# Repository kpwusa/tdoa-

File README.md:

# tdoa-
time distance of arrival direction finder

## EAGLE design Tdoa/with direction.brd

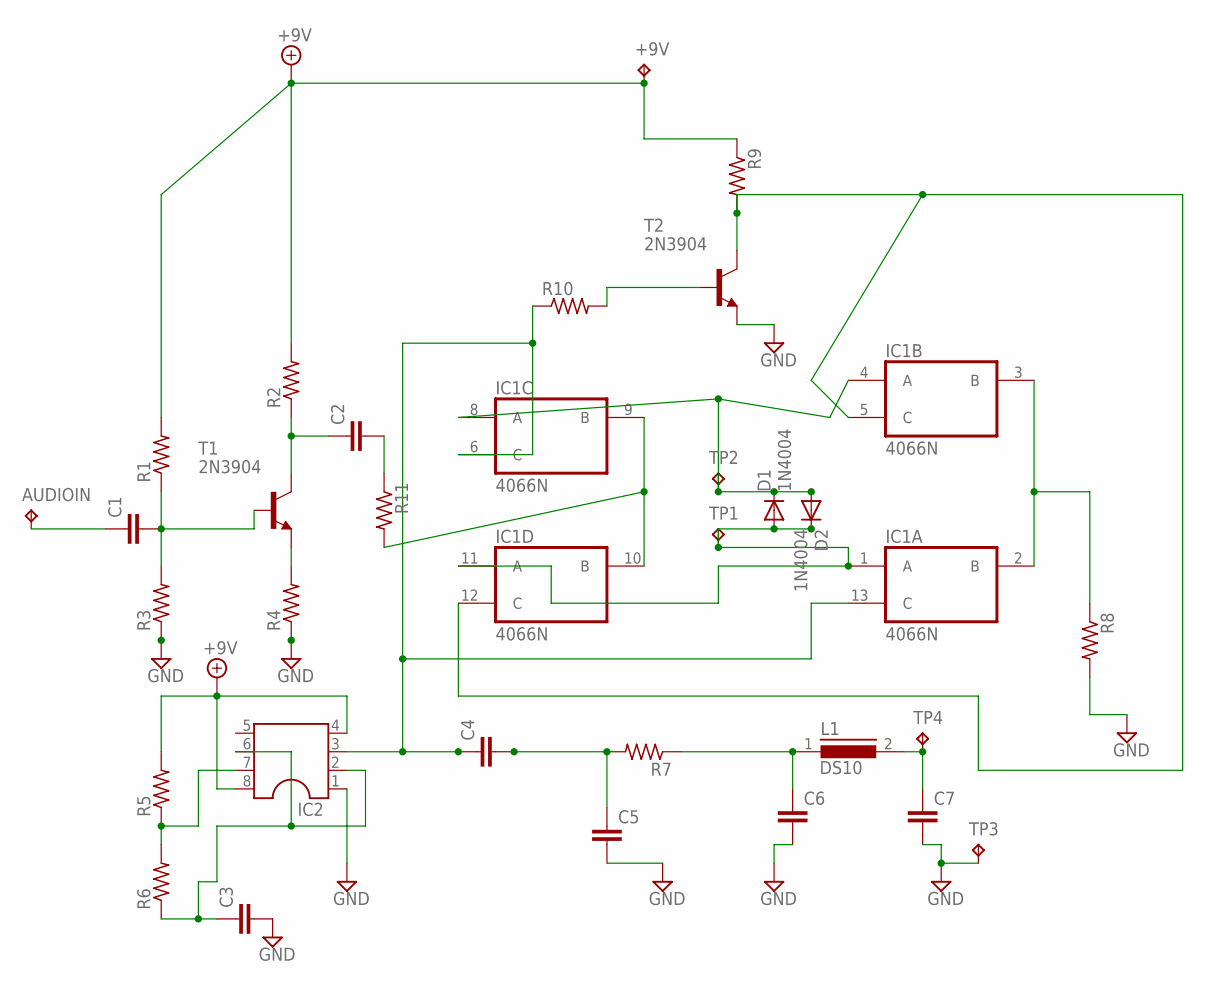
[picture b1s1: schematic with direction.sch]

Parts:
+9V: TPPAD1-17; P1-17
AUDIOIN: TPPAD1-17; P1-17
C1, C2, C7: C10/5; C10B5
C3, C4: C5/2.5; C5B2.5
C5, C6: C5/3; C5B3
D1, D2: 1N4004; DO41-10
IC1: 4066N; DIL14
IC2: DIL8S; SOCKET-08
L1: DS10
R1, R2, R3, R4, R5, R6, R7, R8, R10: R-US_0207/10; 0207/10
R9, R11: R-US_0207/15; 0207/15
T1, T2: 2N3904; TO92
TP1, TP2: TPPAD1-17; P1-17
TP3, TP4: TPPAD1-17Y; P1-17Y

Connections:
+9V: +9V.TP, IC1.14 (VDD), IC2.4, IC2.8, R1.2, R2.2, R5.2, R9.1
unnamed: AUDIOIN.TP, C1.1
unnamed: C1.2, R1.1, R3.2, T1.2 (B)
unnamed: C2.1, R2.1, T1.1 (C)
unnamed: IC1.5 (C), IC1.12 (C), R9.2, T2.1 (C)
unnamed: R10.2, T2.2 (B)
unnamed: C4.1, IC1.6 (C), IC1.13 (C), IC2.3, R10.1
unnamed: D1.C, D2.A, IC1.4 (A), IC1.8 (A), TP2.TP
unnamed: D1.A, D2.C, IC1.1 (A), IC1.11 (A), TP1.TP
unnamed: IC1.9 (B), IC1.10 (B), R11.2
unnamed: C2.2, R11.1
unnamed: IC1.2 (B), IC1.3 (B), R8.1
unnamed: C6.1, L1.1, R7.1
unnamed: C7.1, L1.2, TP4.TP
unnamed: R4.2, T1.3 (E)
unnamed: C4.2, C5.1, R7.2
unnamed: IC2.7, R5.1, R6.2
unnamed: C3.1, IC2.2, IC2.6, R6.1
VSS: C3.2, C5.2, C6.2, C7.2, IC1.7 (VSS), IC2.1, R3.1, R4.1, R8.2, T2.3 (E), TP3.TP

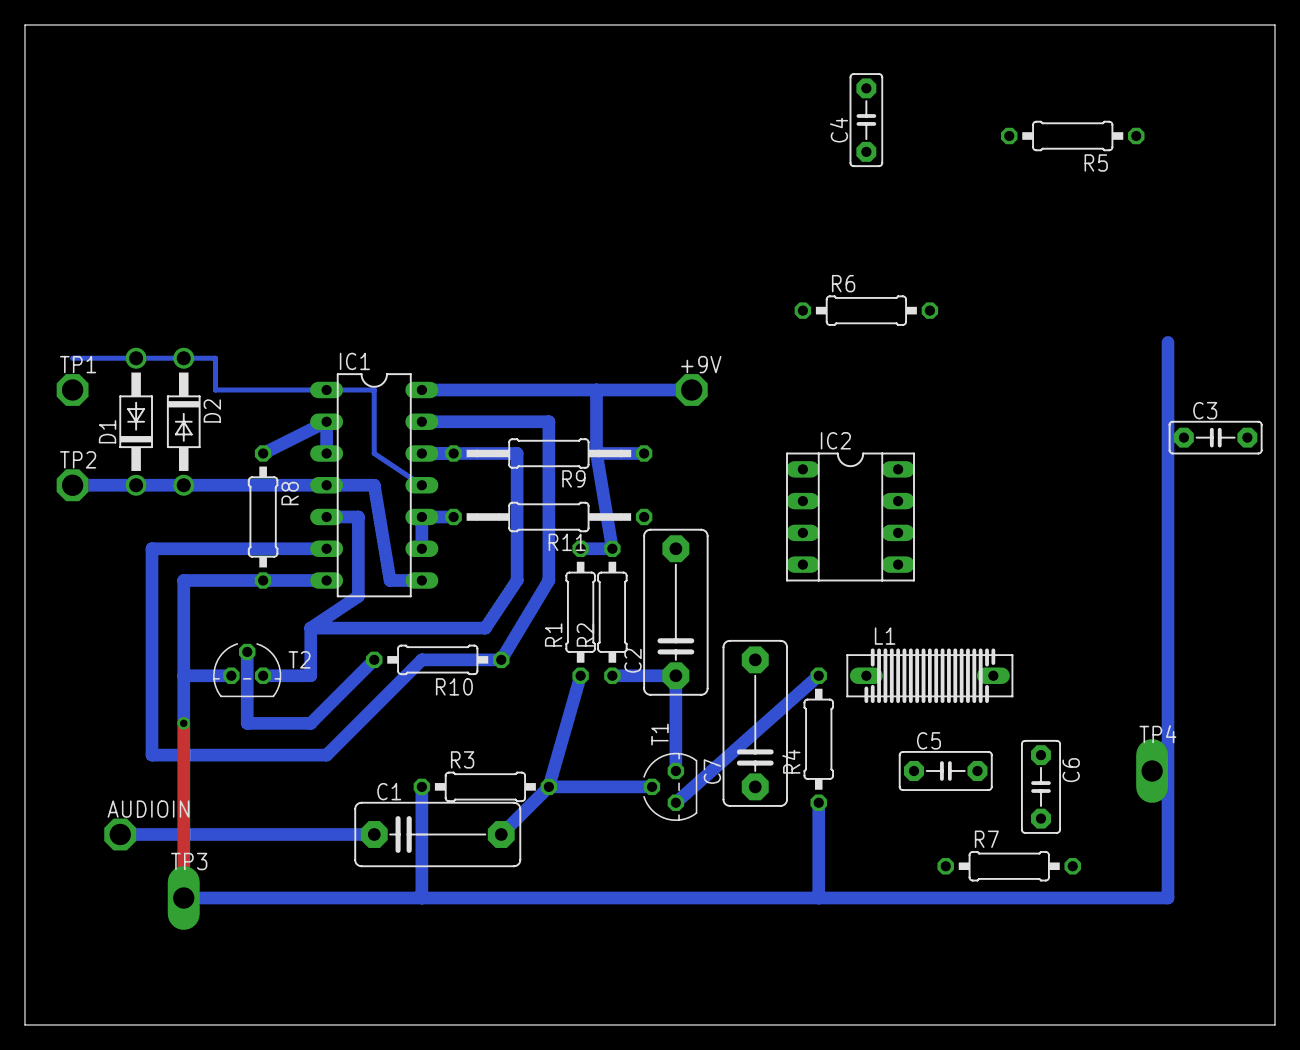
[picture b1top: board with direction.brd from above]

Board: 2 copper layers, 100.0 x 80.0 mm, 31 parts (0 on the bottom side), 19 nets.

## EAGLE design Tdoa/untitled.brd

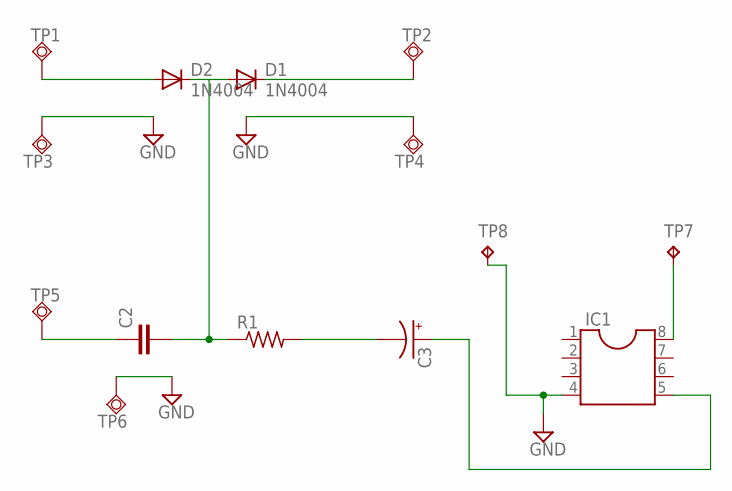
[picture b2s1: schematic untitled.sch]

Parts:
C2: C5/3; C5B3
C3: CPOL-USE5-6; E5-6
D1, D2: 1N4004; DO41-10
IC1: DIL8S; SOCKET-08
R1: R-US_0204/7; 0204/7
TP1, TP2, TP3, TP4, TP5, TP6: TPSQPAD1-20Y; P1-20Y
TP7: TPPAD1-20; P1-20
TP8: TPPAD1-20Y; P1-20Y

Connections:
GND: IC1.4, TP3.TP, TP4.TP, TP6.TP, TP8.TP
unnamed: C3.-, R1.2
unnamed: C2.2, D1.A, D2.C, R1.1
unnamed: C3.+, IC1.5
unnamed: C2.1, TP5.TP
unnamed: IC1.8, TP7.TP
unnamed: D2.A, TP1.TP
unnamed: D1.C, TP2.TP

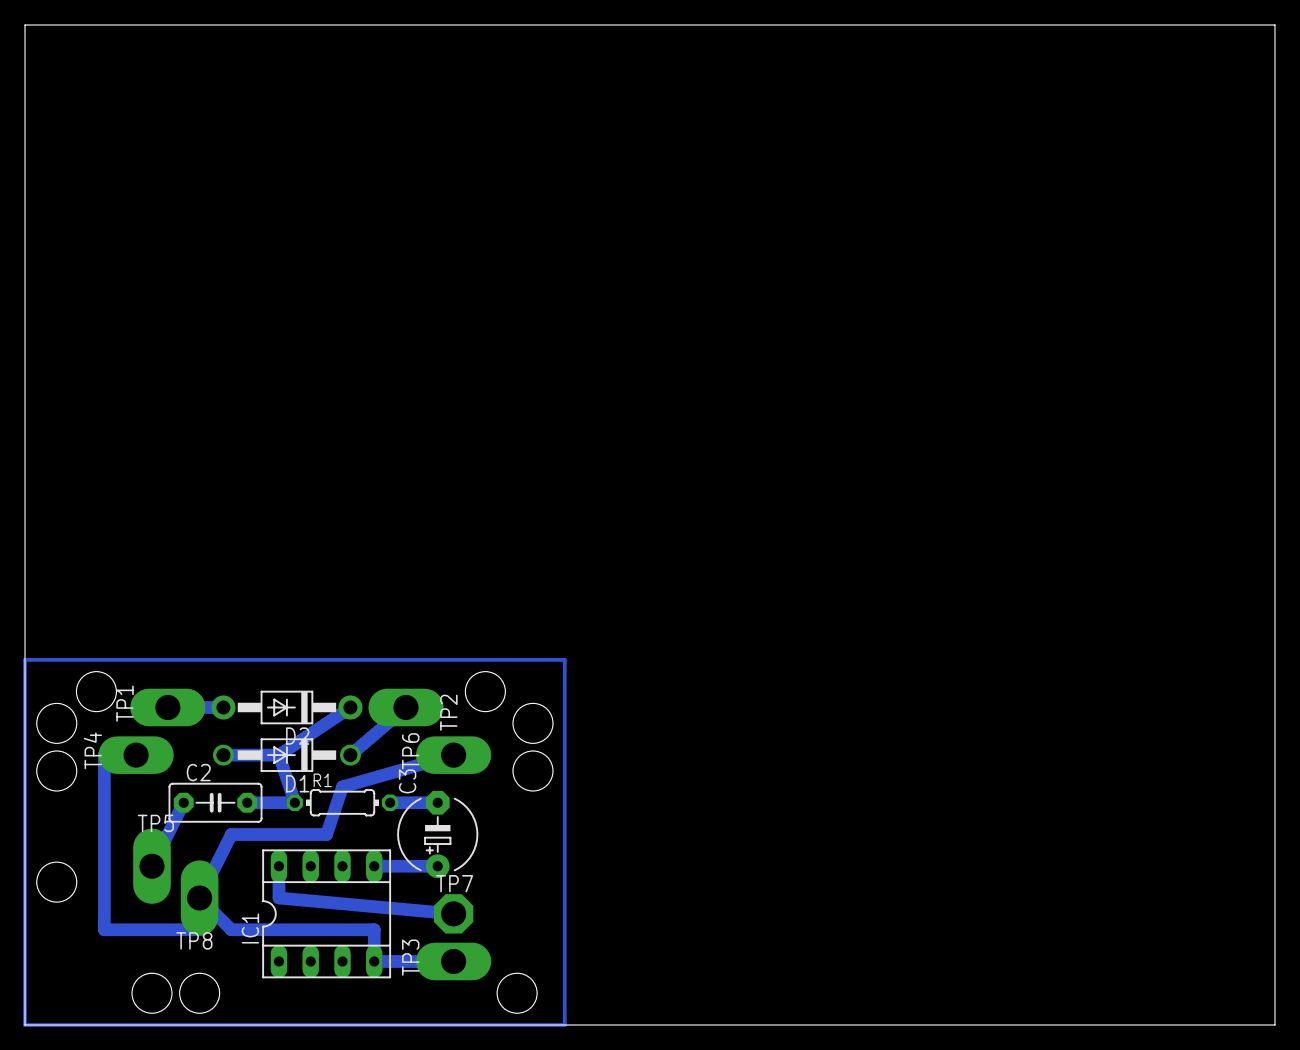
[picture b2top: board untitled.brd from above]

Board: 2 copper layers, 100.0 x 80.0 mm, 14 parts (0 on the bottom side), 8 nets.
